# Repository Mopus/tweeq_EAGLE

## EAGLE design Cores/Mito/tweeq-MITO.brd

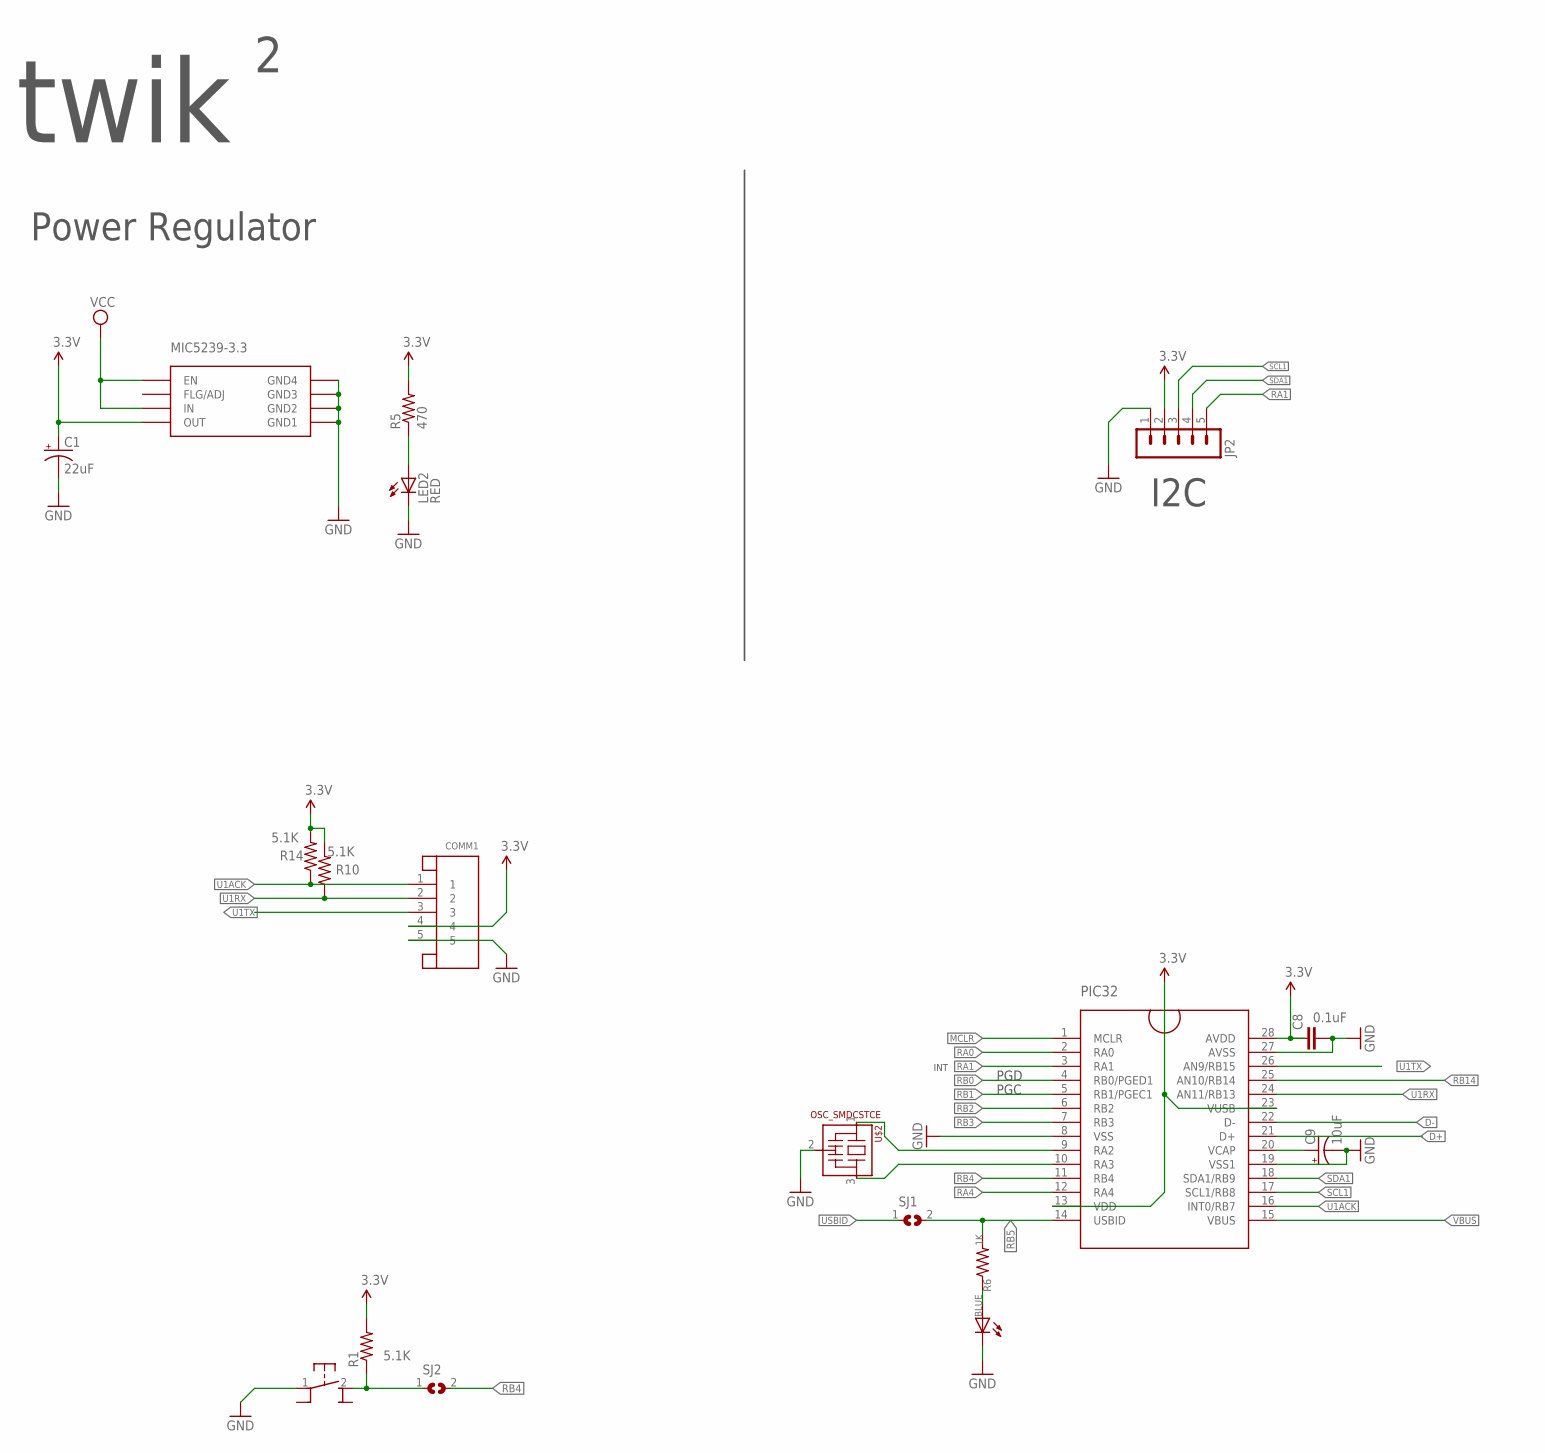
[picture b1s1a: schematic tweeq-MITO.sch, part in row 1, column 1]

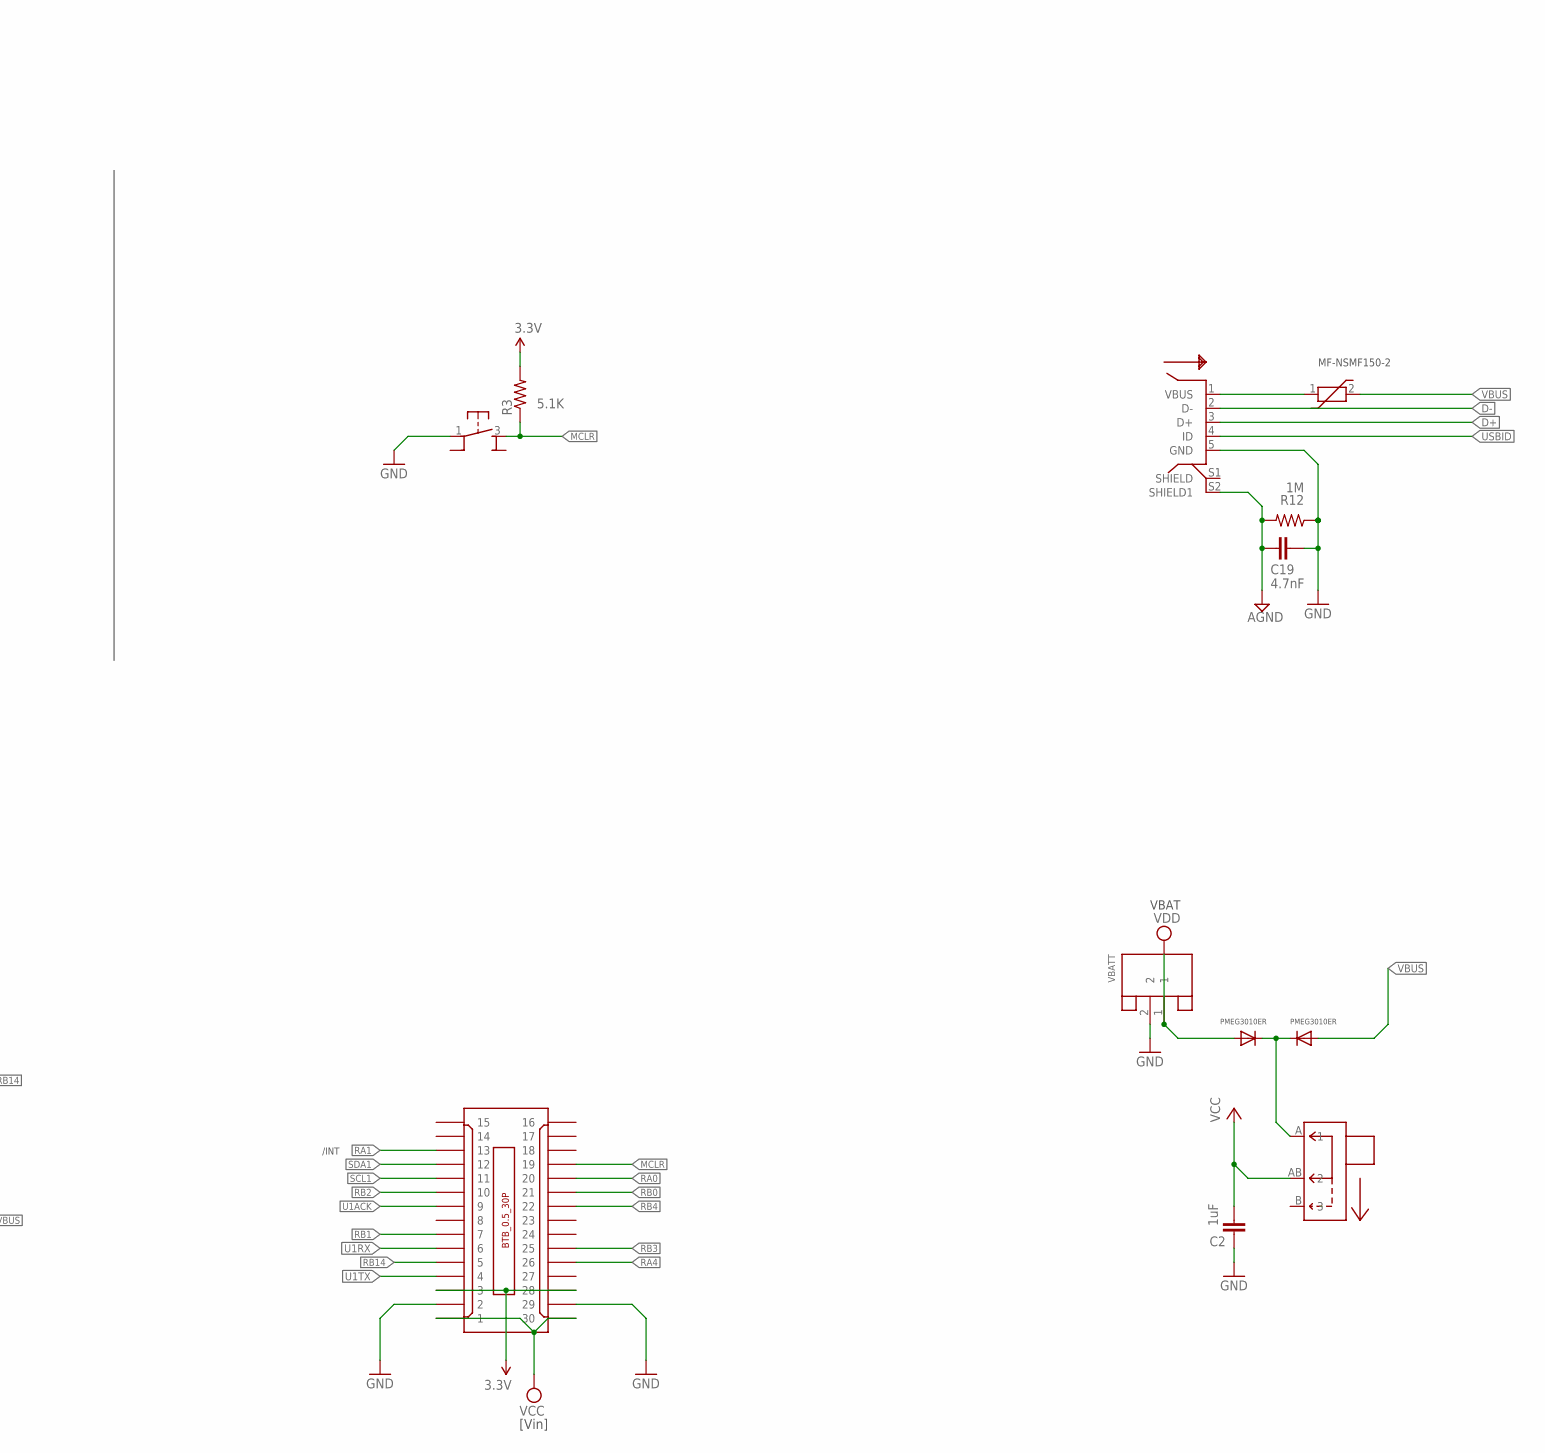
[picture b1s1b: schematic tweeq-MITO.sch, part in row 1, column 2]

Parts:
C1: 22uF; SMC_B
C2: 1uF; C0603K
C8: 0.1uF; C0402K
C9: 10uF; A/3216-18R
C19: 4.7nF; C0402K
COMM1: JST-5PINSH; SH1.0-5PIN
JP2: M05-11.5MM-SMT; 1X05-1.5MM-SMT
LED2: RED; CHIP-LED0603
MIC5239-3.3: MIC5239-MM; MSOP8
PIC32: PIC32MX2_B; SSOP28
PIC_LED: BLUE; CHIP-LED0603
PTC_RESETTABLE_FUSE: PTC_FUSE/MF-NSMF150-2; 1206F
R1, R3, R10, R14: 5.1K; R0402
R5: 470; R0402
R6: 1K; R0402
R12: 1M; R0402
SJ1, SJ2: JUMPER_SJ
U$1: BTB_CONN_30P/M; BTB0.5-30M-3.0G
U$2: OSC_SMDCSTCE; CSTCE_RESONATOR_SMD
U$3: PB_MICRO_SMTRIGHTANGLE; PB_SMT_90D6.2X4.6
U$4: PB_MICRO_SMT; PB_SMT_3.5X3X2
U$7: SLIDE_SWITCH_MINI/MSK1101; MSK1101
U$9, U$10: PMEG3010ER/MOD; SOD123-MOD
U$12: USB/MICRO-5PF-B; MICRO_USB_5PF_B
VBATT: JST-2PINSH; SH1.0-2PIN

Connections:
3.3V: C1.+, C8.1, COMM1.4, JP2.2, MIC5239-3.3.4 (OUT), PIC32.13 (VDD), PIC32.23 (VUSB), PIC32.28 (AVDD), R1.2, R3.2, R5.2, R10.2, R14.2, U$1.3, U$1.28
AGND: C19.2, R12.2, U$12.S2 (SHIELD1)
D+: PIC32.21 (D+), U$12.3 (D+)
D-: PIC32.22 (D-), U$12.2 (D-)
GND: C1.-, C2.1, C8.2, C9.-, C19.1, COMM1.5, JP2.1, LED2.C, MIC5239-3.3.5 (GND1), MIC5239-3.3.6 (GND2), MIC5239-3.3.7 (GND3), MIC5239-3.3.8 (GND4), PIC32.8 (VSS), PIC32.19 (VSS1), PIC32.27 (AVSS), PIC_LED.C, R12.1, U$1.2, U$1.29, U$2.2 (VSS), U$3.1, U$4.1, U$12.5 (GND), VBATT.2
MCLR: PIC32.1 (MCLR), R3.1, U$1.19, U$4.3 (2)
unnamed: R1.1, SJ2.1, U$3.2
unnamed: PIC32.9 (RA2), U$2.1
unnamed: PIC_LED.A, R6.1
unnamed: C9.+, PIC32.20 (VCAP)
unnamed: U$7.A (1), U$9.C, U$10.C
unnamed: PIC32.10 (RA3), U$2.3
unnamed: PTC_RESETTABLE_FUSE.1, U$12.1 (VBUS)
unnamed: LED2.A, R5.1
RA0: PIC32.2 (RA0), U$1.20
RA1: JP2.5, PIC32.3 (RA1), U$1.13
RA4: PIC32.12 (RA4), U$1.26
RB0: PIC32.4 (RB0/PGED1), U$1.21
RB1: PIC32.5 (RB1/PGEC1), U$1.7
RB2: PIC32.6 (RB2), U$1.10
RB3: PIC32.7 (RB3), U$1.25
RB4: PIC32.11 (RB4), SJ2.2, U$1.22
RB5: PIC32.14 (USBID), R6.2, SJ1.2
RB14: PIC32.25 (AN10/RB14), U$1.5
SCL1: JP2.3, PIC32.17 (SCL1/RB8), U$1.11
SDA1: JP2.4, PIC32.18 (SDA1/RB9), U$1.12
U1ACK: COMM1.1, PIC32.16 (INT0/RB7), R14.1, U$1.9
U1RX: COMM1.2, PIC32.24 (AN11/RB13), R10.1, U$1.6
U1TX: COMM1.3, PIC32.26 (AN9/RB15), U$1.4
USBID: SJ1.1, U$12.4 (ID)
VBUS: PIC32.15 (VBUS), PTC_RESETTABLE_FUSE.2, U$10.A
VCC: C2.2, MIC5239-3.3.1 (EN), MIC5239-3.3.3 (IN), U$1.1, U$1.30, U$7.AB (2)
VDD: U$9.A, VBATT.1

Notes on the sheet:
PGC
PGD
I2C
Power Regulator
twik
[Vin]
INT
/INT
MF-NSMF150-2
PMEG3010ER
VBAT

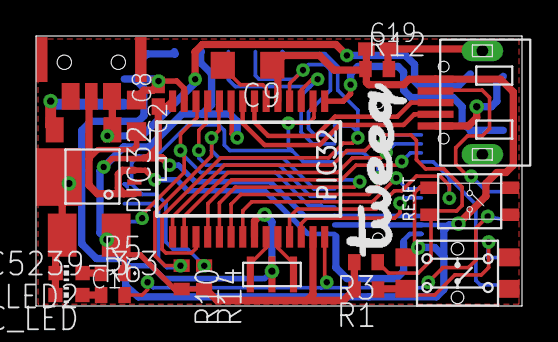
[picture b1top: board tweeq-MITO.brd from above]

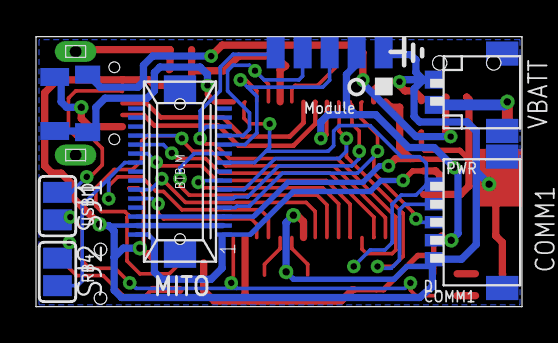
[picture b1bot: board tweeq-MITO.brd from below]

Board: 2 copper layers, 27.0 x 15.0 mm, 31 parts (8 on the bottom side), 33 nets.

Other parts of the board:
U$6: TWEEQ-LOGO-M

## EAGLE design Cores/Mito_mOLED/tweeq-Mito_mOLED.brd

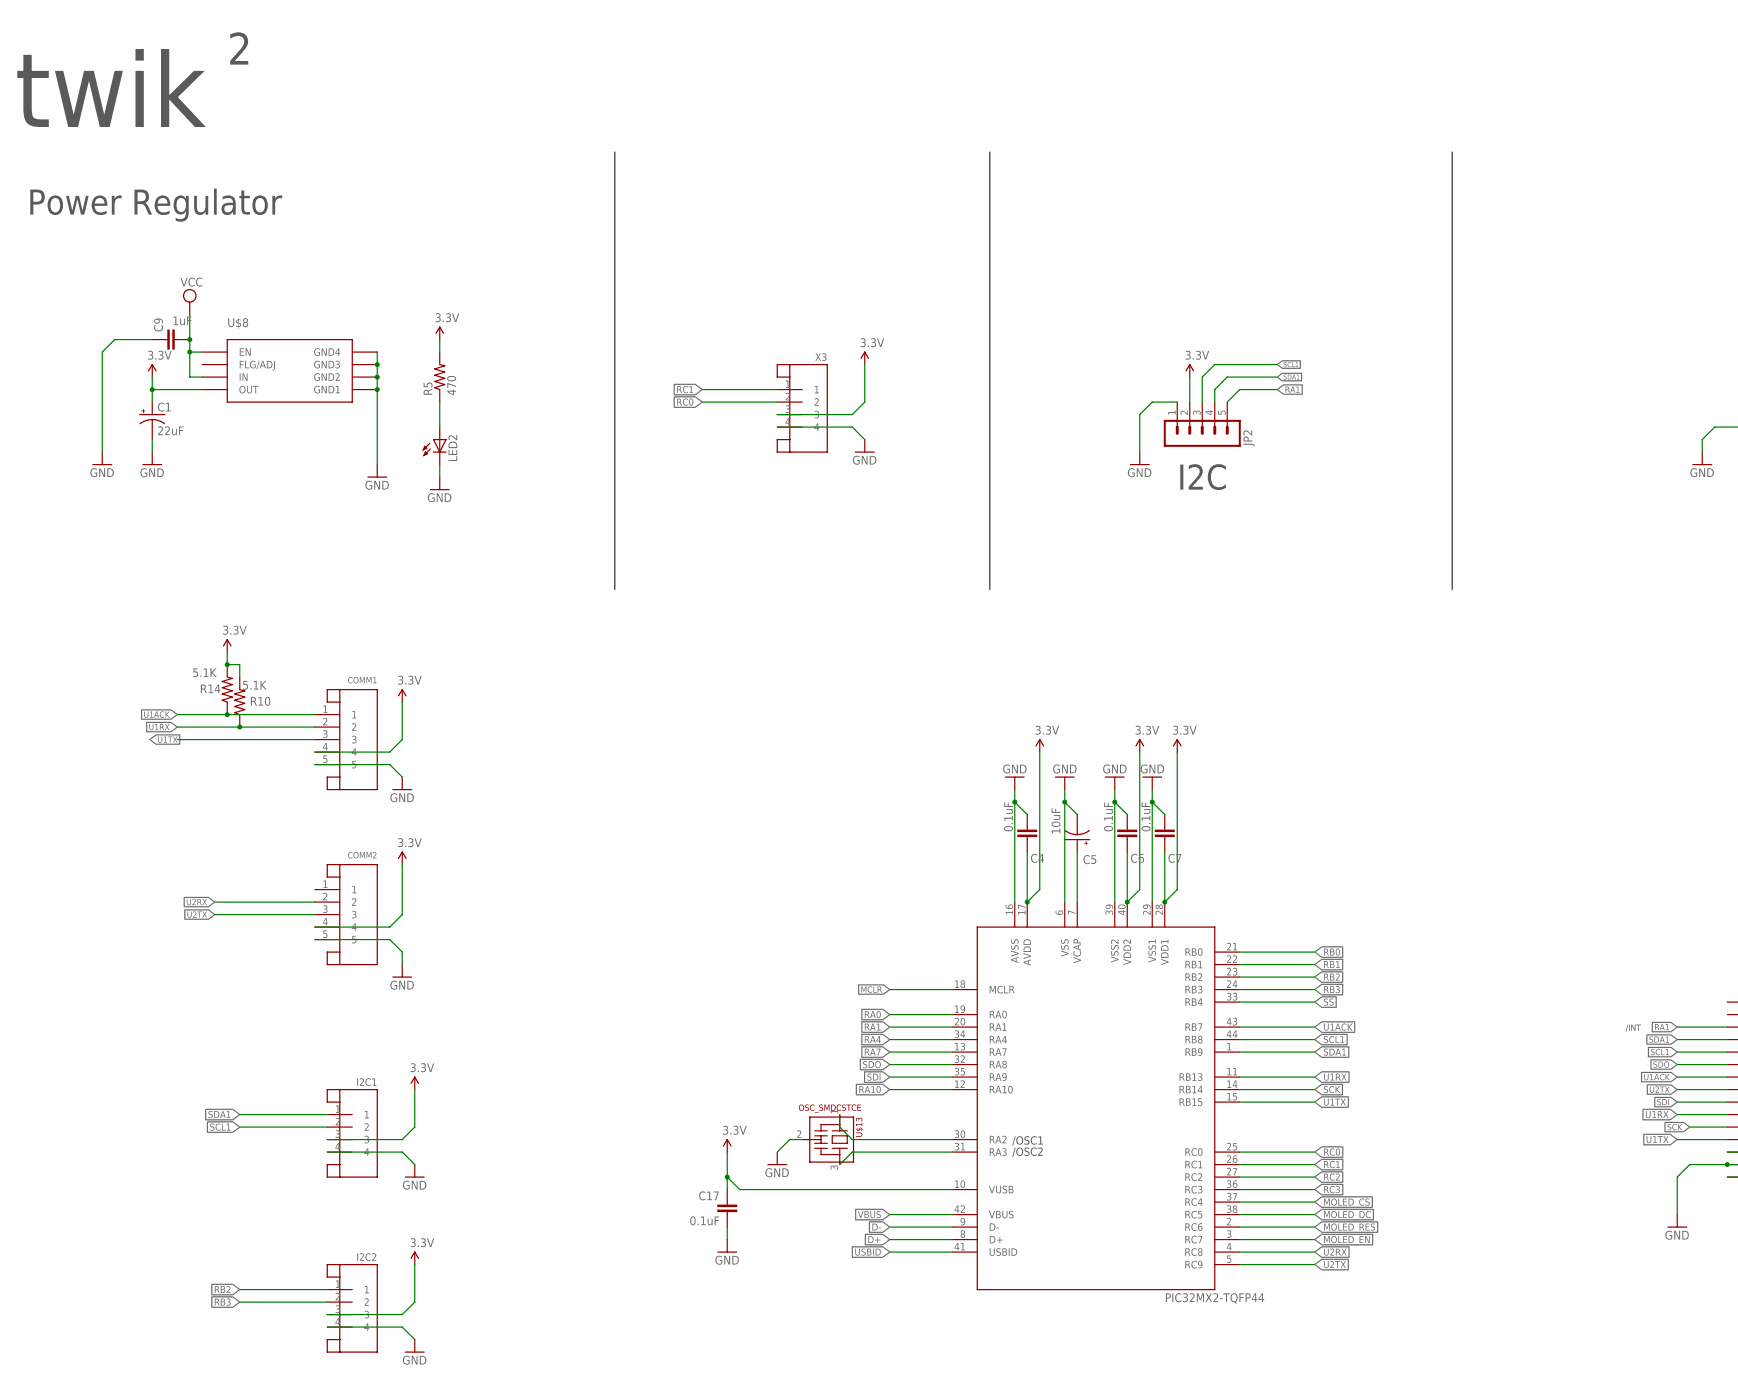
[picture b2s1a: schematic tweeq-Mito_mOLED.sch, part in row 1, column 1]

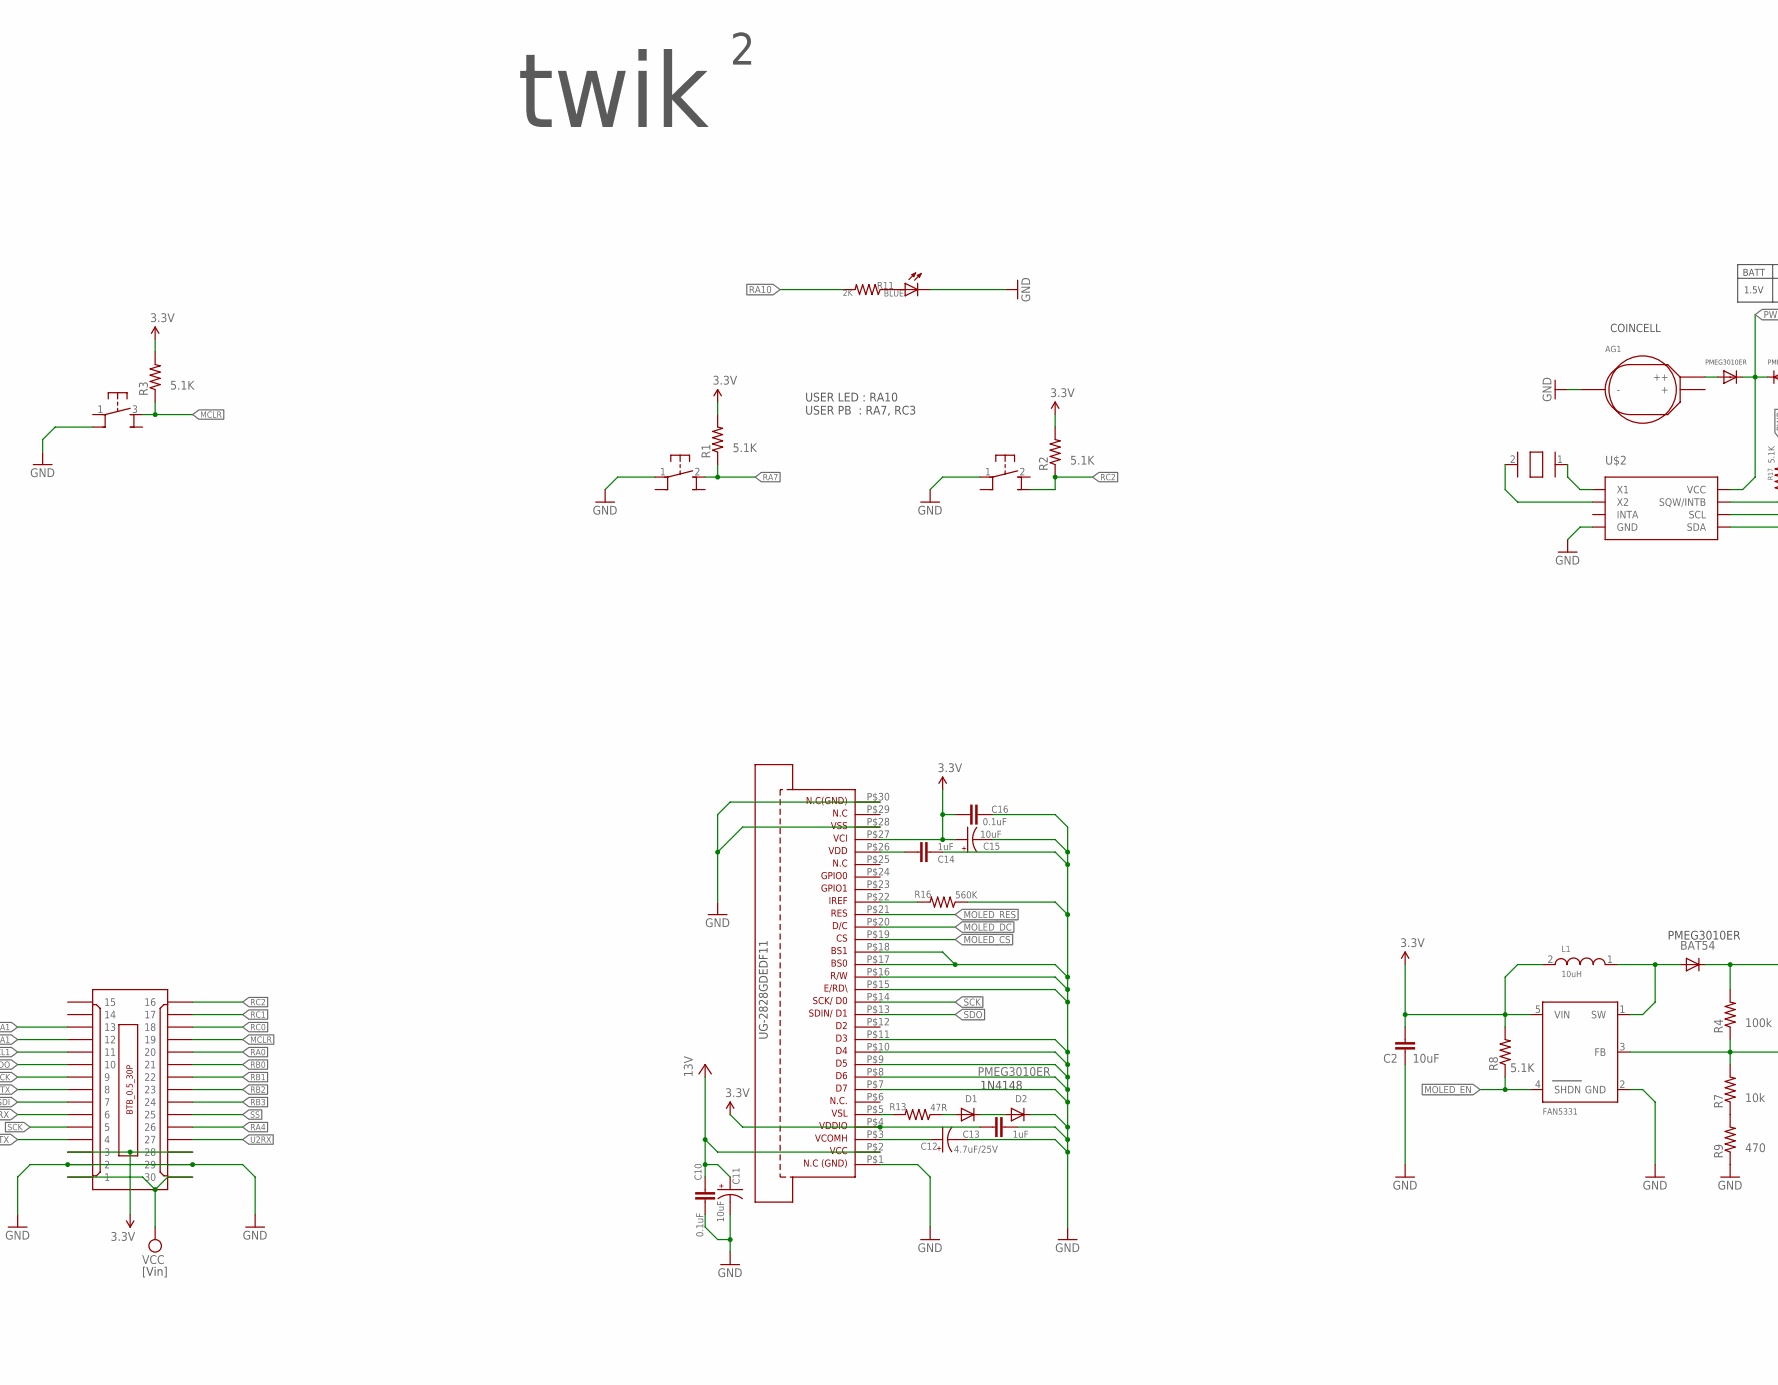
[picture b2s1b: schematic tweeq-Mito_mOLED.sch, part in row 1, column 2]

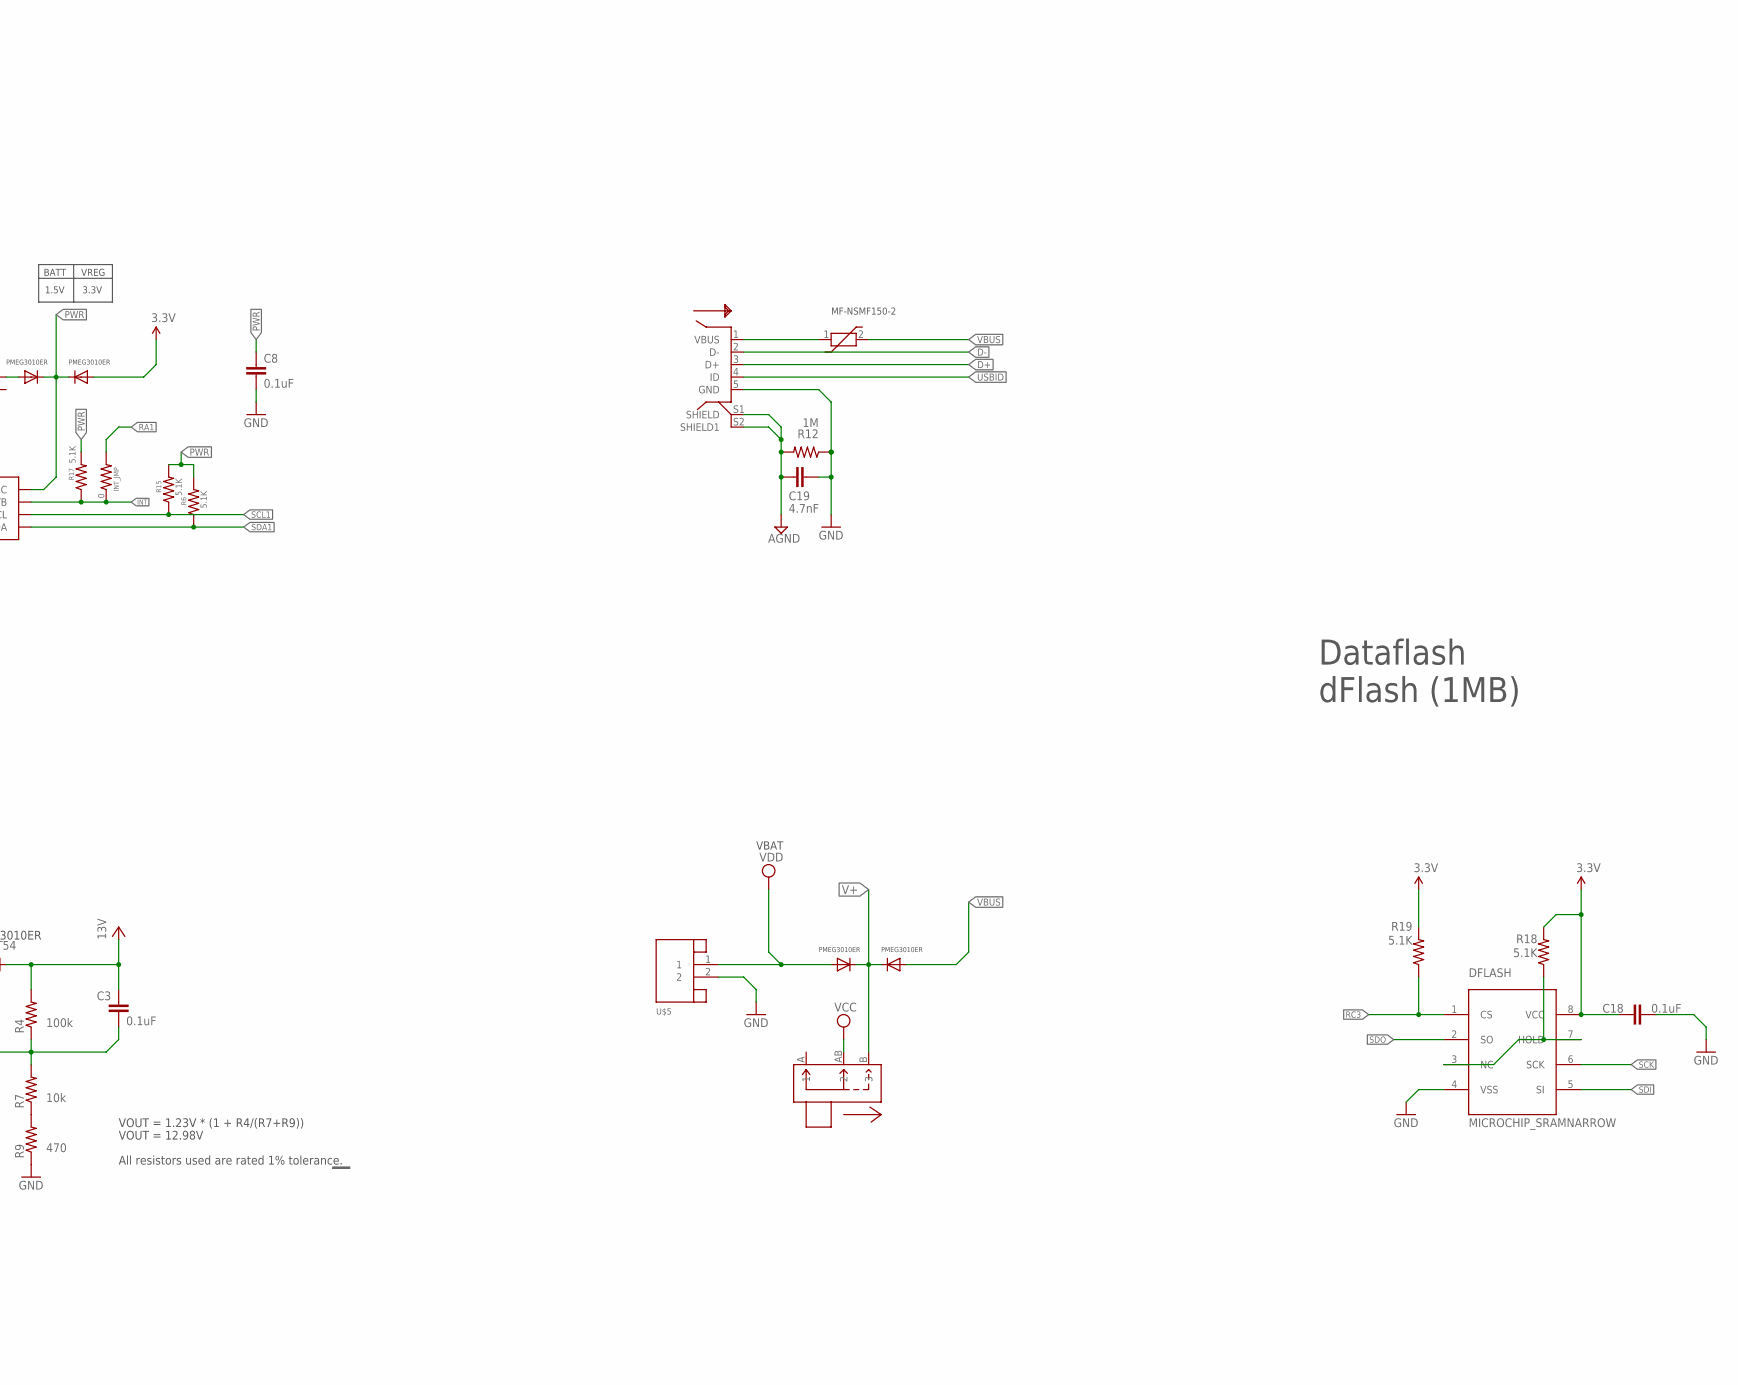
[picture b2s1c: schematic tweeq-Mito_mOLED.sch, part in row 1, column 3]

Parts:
AG1: BATT_COMMONAG1_SMD; BATT_AG1_SMD
BAT54: SOD123
C1: 22uF; SMC_B
C2: 10uF; C0603K
C3, C10, C16: 0.1uF; C0603K
C4, C6, C7, C8, C17, C18: 0.1uF; C0402K
C5, C11, C15: 10uF; A/3216-18R
C9: 1uF; C0603K
C12: 4.7uF/25V; A/3216-18R
C13, C14: 1uF; C0402K
C19: 4.7nF; C0402K
COMM1, COMM2: JST-5PINSH; SH1.0-5PIN
D1, D2: PMEG3010ER; SOD123
DFLASH: MICROCHIP_SRAMNARROW; SOIC8
FAN5331: FAN5331; SOT23-5
I2C1, I2C2: JST-4PINSH; SH1.0-4PIN
INT_JMP: 0; R0402
JP2: M05-11.5MM-SMT; 1X05-1.5MM-SMT
L1: 10uH; 2518_1007
LED2: LEDCHIP-LED0603; CHIP-LED0603
PIC_LED1: BLUE; CHIP-LED0805
PTC_RESETTABLE_FUSE: PTC_FUSE/MF-NSMF150-2; 1206F
R1, R2, R3, R6, R8, R10, R14, R15, R17, R18, R19: 5.1K; R0402
R4: 100k; R0402
R5, R9: 470; R0402
R7: 10k; R0402
R11: 2K; R0402
R12: 1M; R0402
R13: 47R; R0402
R16: 560K; R0402
U$1: BTB_CONN_30P/M; BTB0.5-30M-3.0G
U$2: DS1337SO; MSOP8
U$3, U$9: PB_MICRO_SMTRIGHTANGLE; PB_SMT_90D6.2X4.6
U$4: PB_MICRO_SMT; PB_SMT_3.5X3X2
U$5: JST-2PINSH; SH1.0-2PIN
U$7: SLIDE_SWITCH_MINI/MSK1101; MSK1101
U$8: MIC5239-MM; MSOP8
U$10, U$14, U$16, U$17: PMEG3010ER/MOD; SOD123-MOD
U$11: PIC32MX2-TQFP44; QFP80P1200X1200X120-44N
U$12: USB/MICRO-5PF-B; MICRO_USB_5PF_B
U$13: OSC_SMDCSTCE; CSTCE_RESONATOR_SMD
U$15: 32.765KHZ_CRYSTALABS07; ABS07
UG-2828GDEDF11: FPC_CONN_30P-XF2M; XF2M-3015-1A
X3: JST-4PINSH; SH1.0-4PIN

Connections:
3.3V: C1.+, C2.2, C4.1, C6.1, C7.1, C13.2, C15.+, C16.2, C17.1, C18.1, COMM1.4, COMM2.4, DFLASH.8 (VCC), FAN5331.5 (VIN), I2C1.3, I2C2.3, JP2.2, L1.2, R1.2, R2.2, R3.2, R5.2, R8.2, R10.2, R14.2, R18.2, R19.2, U$1.3, U$1.28, U$8.4 (OUT), U$11.10 (VUSB), U$11.17 (AVDD), U$11.28 (VDD1), U$11.40 (VDD2), U$17.A, UG-2828GDEDF11.P$4, UG-2828GDEDF11.P$27, X3.3
13V: BAT54.C, C3.2, C10.2, C11.+, R4.2, UG-2828GDEDF11.P$2
AGND: C19.2, R12.2, U$12.S1 (SHIELD), U$12.S2 (SHIELD1)
D+: U$11.8 (D+), U$12.3 (D+)
D-: U$11.9 (D-), U$12.2 (D-)
GND: AG1.-, C1.-, C2.1, C4.2, C5.-, C6.2, C7.2, C8.2, C9.1, C10.1, C11.-, C12.-, C13.1, C14.1, C15.-, C16.1, C17.2, C18.2, C19.1, COMM1.5, COMM2.5, D2.C, DFLASH.4 (VSS), FAN5331.2 (GND), I2C1.4, I2C2.4, JP2.1, LED2.C, PIC_LED1.C, R9.1, R12.1, R16.1, U$1.2, U$1.29, U$2.4 (GND), U$3.1, U$4.2 (1A), U$5.2, U$8.5 (GND1), U$8.6 (GND2), U$8.7 (GND3), U$8.8 (GND4), U$9.1, U$11.6 (VSS), U$11.16 (AVSS), U$11.29 (VSS1), U$11.39 (VSS2), U$12.5 (GND), U$13.2 (VSS), UG-2828GDEDF11.P$1 (N.C(GND)), UG-2828GDEDF11.P$7, UG-2828GDEDF11.P$8, UG-2828GDEDF11.P$9, UG-2828GDEDF11.P$10, UG-2828GDEDF11.P$11, UG-2828GDEDF11.P$15, UG-2828GDEDF11.P$16, UG-2828GDEDF11.P$17, UG-2828GDEDF11.P$18, UG-2828GDEDF11.P$28, UG-2828GDEDF11.P$30, X3.4
INT: INT_JMP.1, R17.1, U$2.7 (SQW/INTB)
MCLR: R3.1, U$1.19, U$4.3 (2), U$11.18 (MCLR)
MOLED_CS: U$11.37 (RC4), UG-2828GDEDF11.P$19
MOLED_DC: U$11.38 (RC5), UG-2828GDEDF11.P$20
MOLED_EN: FAN5331.4 (SHDN), R8.1, U$11.3 (RC7)
MOLED_RES: U$11.2 (RC6), UG-2828GDEDF11.P$21
unnamed: BAT54.A, FAN5331.1 (SW), L1.1
unnamed: U$2.2 (X2), U$15.2
unnamed: U$2.1 (X1), U$15.1
unnamed: DFLASH.3 (NC), DFLASH.7 (HOLD), R18.1
unnamed: R7.1, R9.2
unnamed: C3.1, FAN5331.3 (FB), R4.1, R7.2
unnamed: U$11.31 (RA3), U$13.3
unnamed: U$11.30 (RA2), U$13.1
unnamed: C5.+, U$11.7 (VCAP)
unnamed: R16.2, UG-2828GDEDF11.P$22
unnamed: PIC_LED1.A, R11.1
unnamed: C12.+, UG-2828GDEDF11.P$3
unnamed: D1.C, D2.A
unnamed: PTC_RESETTABLE_FUSE.1, U$12.1 (VBUS)
unnamed: R13.2, UG-2828GDEDF11.P$5
unnamed: D1.A, R13.1
unnamed: C14.2, UG-2828GDEDF11.P$26
unnamed: LED2.A, R5.1
PWR: C8.1, R6.2, R15.2, R17.2, U$2.8 (VCC), U$16.C, U$17.C
RA0: U$1.20, U$11.19 (RA0)
RA1: INT_JMP.2, JP2.5, U$1.13, U$11.20 (RA1)
RA4: U$1.26, U$11.34 (RA4)
RA7: R1.1, U$3.2, U$11.13 (RA7)
RA10: R11.2, U$11.12 (RA10)
RB0: U$1.21, U$11.21 (RB0)
RB1: U$1.22, U$11.22 (RB1)
RB2: I2C2.1, U$1.23, U$11.23 (RB2)
RB3: I2C2.2, U$1.24, U$11.24 (RB3)
RC0: U$1.18, U$11.25 (RC0), X3.2
RC1: U$1.17, U$11.26 (RC1), X3.1
RC2: R2.1, U$1.16, U$9.2A, U$11.27 (RC2)
RC3: DFLASH.1 (CS), R19.1, U$11.36 (RC3)
SCK: DFLASH.6 (SCK), U$1.5, U$11.14 (RB14), UG-2828GDEDF11.P$14
SCL1: I2C1.2, JP2.3, R15.1, U$1.11, U$2.6 (SCL), U$11.44 (RB8)
SDA1: I2C1.1, JP2.4, R6.1, U$1.12, U$2.5 (SDA), U$11.1 (RB9)
SDI: DFLASH.5 (SI), U$1.7, U$11.35 (RA9)
SDO: DFLASH.2 (SO), U$1.10, U$11.32 (RA8), UG-2828GDEDF11.P$13
SS: U$1.25, U$11.33 (RB4)
U1ACK: COMM1.1, R14.1, U$1.9, U$11.43 (RB7)
U1RX: COMM1.2, R10.1, U$1.6, U$11.11 (RB13)
U1TX: COMM1.3, U$1.4, U$11.15 (RB15)
U2RX: COMM2.2, U$1.27, U$11.4 (RC8)
U2TX: COMM2.3, U$1.8, U$11.5 (RC9)
USBID: U$11.41 (USBID), U$12.4 (ID)
V+: U$7.B (3), U$10.C, U$14.C
VBAT: AG1.+2 (++), U$16.A
VBUS: PTC_RESETTABLE_FUSE.2, U$11.42 (VBUS), U$14.A
VCC: C9.2, U$1.1, U$1.30, U$7.AB (2), U$8.1 (EN), U$8.3 (IN)
VDD: U$5.1, U$10.A

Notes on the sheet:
I2C
Power Regulator
twik
[Vin]
/INT
/OSC1
/OSC2
VOUT = 1.23V * (1 + R4/(R7+R9))
VOUT = 12.98V
All resistors used are rated 1% tolerance.
N.C (GND)
VCC
VCOMH
VDDIO
VSL
N.C.
E/RD\
R/W
BS0
BS1
D/C
RES
IREF
GPIO1
GPIO0
N.C
VDD
VCI
VSS
N.C(GND)
USER LED : RA10 USER PB : RA7, RC3
UG-2828GDEDF11
1N4148
SCK/
SDIN/
PMEG3010ER
MF-NSMF150-2
VBAT
COINCELL
1.5V

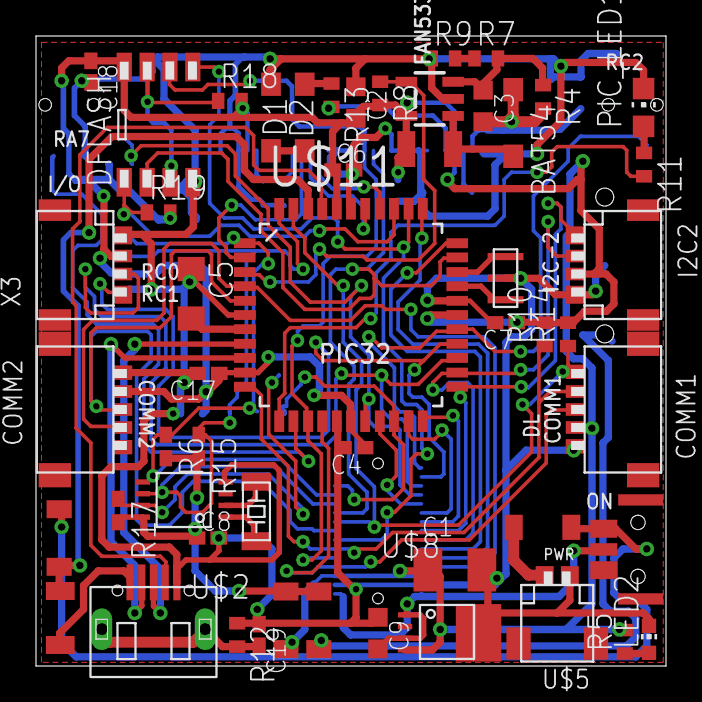
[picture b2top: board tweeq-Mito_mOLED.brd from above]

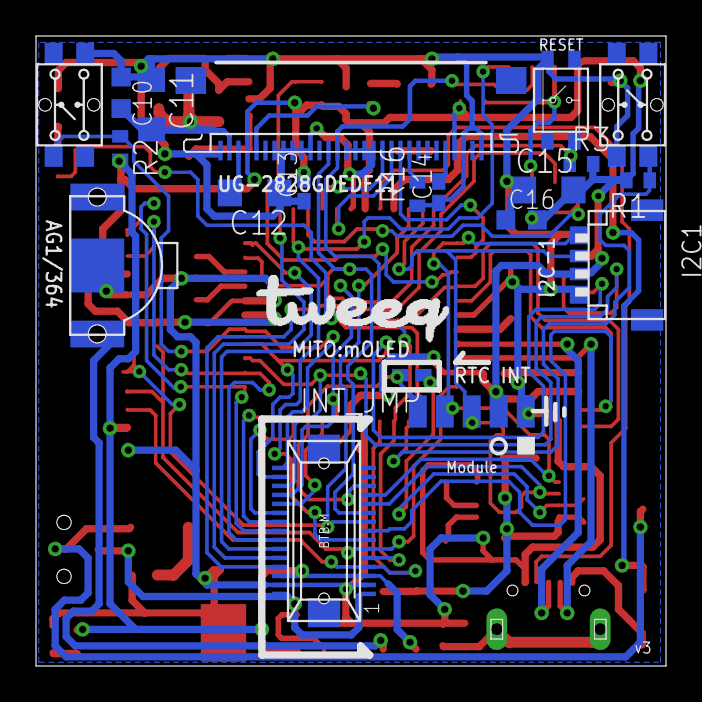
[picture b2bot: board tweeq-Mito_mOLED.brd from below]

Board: 2 copper layers, 35.0 x 35.0 mm, 73 parts (21 on the bottom side), 61 nets.

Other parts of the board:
U$18: TWEEQ-LOGO-L

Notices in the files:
parts and their libraries:
microbuilder: This work is placed in the public domain, and may be freely used for commercial and non-commercial work with the following conditions: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
